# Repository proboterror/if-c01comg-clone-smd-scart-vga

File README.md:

IF-C01COMG Clone board SMD Full size - with SCART and DSUB-15 (VGA 15KHz) inputs.<br>
Separate H/V and combined sync supported for DSUB-15 input.

BNC connectors option removed<br>
RCA audio connectors replaced with 3.5 mm audio jack<br>
Switches changed to ALPS SPUJ190900 / SPUJ193700<br>

Project migrated to KiCad 8.

## Bill of materials
|Reference|Value|Footprint|Qty|Manufacturer|SKU|
|-----|-----|-----|-----|-----|-----|
|C101,C102,C103|47uF/25V|6.3x5.4|3|PANASONIC|EEEFK1H470XP|
|||||PANASONIC|EEEFK1E470P|
|||||PANASONIC|EEEFK1E470P|
|C104,C105|10uF/50V|5x5.4|2|PANASONIC|EEEFK1H100UR|
|C114,C116,C117,C118,C119,C206|100nF|805|6|MURATA|GRM21BR71H104KA01L|
|C115,C207|100uF/16V|6.3x5.4|2|PANASONIC|EEEFK1C101P|
|C120,C122|10uF/25V|5x5.4|2|PANASONIC|EEEFK1H100UR|
|C121|1uF/25V|805|1|SAMSUNG|CL21B105KBFNNNE|
|C201,C202,C205|180pF|805|3|MURATA|GRM2165C1H181J|
|C203|1uF/50V|4x5.4|1|JB Capacitors|JCK1H010M040054|
|C204|39pF|805|1|MURATA|GRM2165C1H390J|
|D101,D102,D103,D104,D105,D106,D107,D108,D109,D110|BAT46-TR (BAT46W)|SOD-123|10|Diodes|BAT46W-7-F|
|D201|BZT52C12 (12V Zener)|SOD-123|1|Diodes|BZT52C12|
|F1|1812L050PR|Fuse_1812_4532Metric|1|Littlefuse|1812L050PR|
|J1|Conn_02x25_Odd_Even|Pin_Header_Angled_2x25_Pitch2.54mm|1|Connfly|BH-50R (DS1013-50R) (IDC-50MR)|
|J2|SCART-F||1|NINIGI|SCART-17|
|J5|DE15||1||DB15 Female Pins offset 8.5 mm Rows step 2.54 mm|
|J6|SJ1-3535NG||1|KLS Electronic|KLS1-TSJ3.5-008CBA (ST-215N-03)|
|||||KLS Electronic|KLS1-TSJ3.5-008DC (ST-215N-04)|
|||||Dragon City|ST-215N-03/ST-215N-04/ST-215N-03-SL|
|K1|G6K-2PY-12DC||1|OMRON|G6K-2PY-12DC|
|Q101,Q105,Q109,Q113,Q114,Q201|BC850C|SOT-23|6|Diotec|BC850C|
|R1,R2|470R|805|2|YAGEO|RC0805FR-07470RL|
|R3|20K|805|1|ROYAL OHM|0805S8F2002T5E|
|R101,R115,R129,R143,R152|75|805|5|ROYAL OHM|0805S8F750JT5E|
|R104,R114,R118,R128,R132,R142,R146,R155|100|805|8|YAGEO|RC0805FR-07100RL|
|R105,R119,R133,R203|56k|805|4|YAGEO|RC0805FR-0756KL|
|R106,R120,R134,R147,R148,R156,R157|33k|805|7|YAGEO|RC0805FR-0733KL|
|R107,R121,R135|1.5k|805|3|ROYAL OHM|0805S8F1501T5E|
|R113,R127,R141|390|805|3|YAGEO|RC0805FR-07390RL|
|R149,R158,R205|2.7k|805|3|YAGEO|RC0805FR-072K7L|
|R202|1K|805|1|ROYAL OHM|0805S8F1001T5E|
|R204|68K|805|1|YAGEO|RC0805FR-0768KL|
|SW1|SW_DPDT_x2||1|ALPS|SPUJ190900|
|SW2|SPUJ193700||1|ALPS|SPUJ193700|
|U1|NCP1117-12_SOT223|SOT-223|1|ONSEMI|NCP1117ST12T3G|

IF-C01COMG Clone board SMD Full size

This is a full sized version of the IF-C01COMG board for JVC pro monitors (TM-Hxx50CG) and some others...

It's basically the THT base board I made some months ago, with most components changed to SMD.

Credit goes to James Vanderloeff for the dual input idea.

Board is for now completely untested...

Finally this is a Kicad 5.1 project :D

You're welcome to clone, sell, re-design and whatever, see LICENSE.

(2021) Martin Hejnfelt (martin@hejnfelt.com)
This work is free. You can redistribute it and/or modify it under the
terms of the Do What The Fuck You Want To Public License, Version 2,
as published by Sam Hocevar. See the LICENSE file for more details.

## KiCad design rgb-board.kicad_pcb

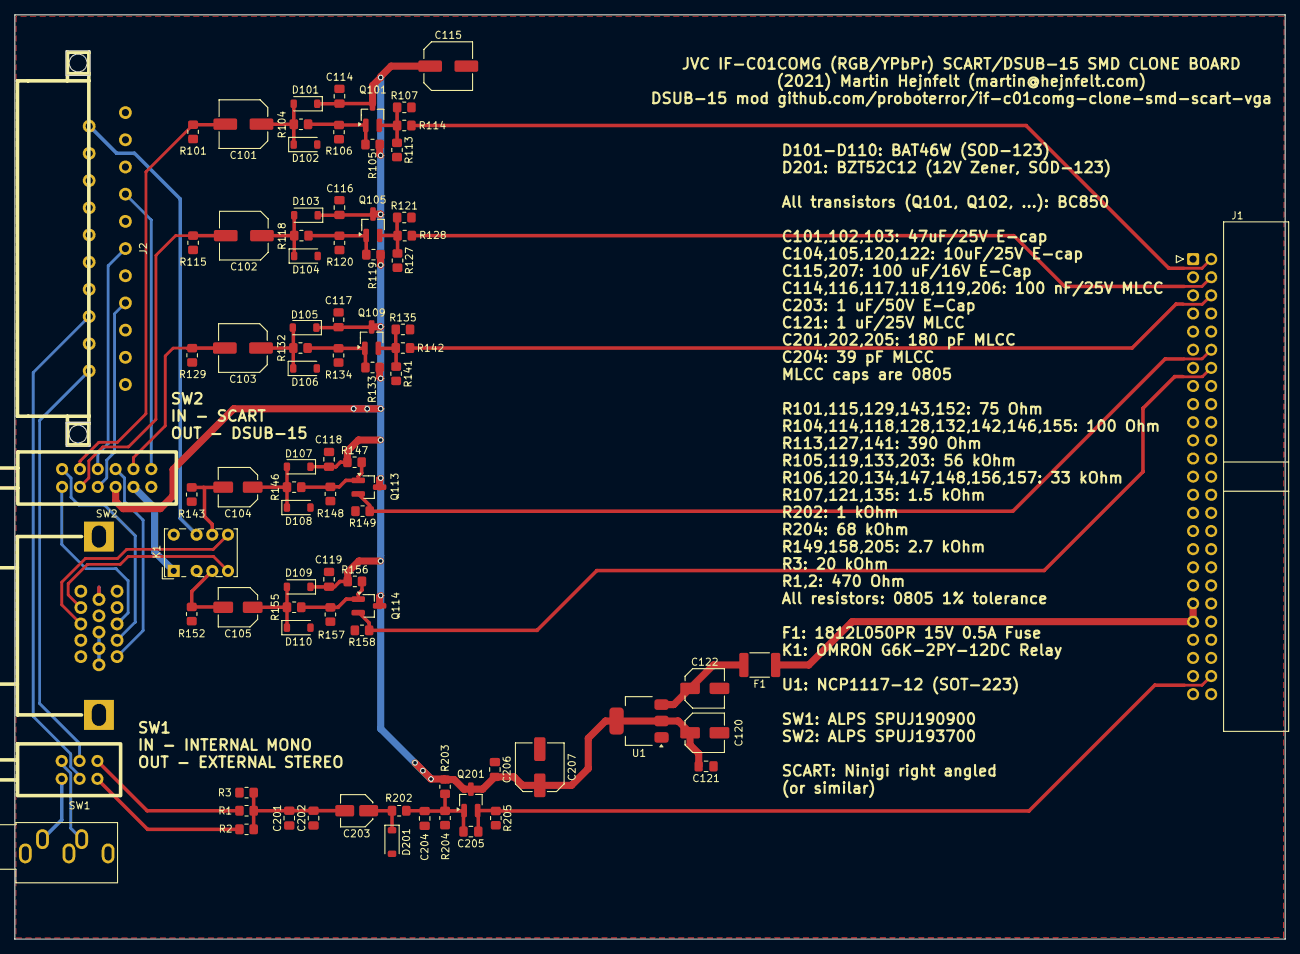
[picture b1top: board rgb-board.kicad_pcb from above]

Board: 2 copper layers, 178.0 x 129.5 mm, 85 parts (0 on the bottom side), 47 nets.

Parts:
C101, C102, C103: 47uF/25V; C_Elec_6.3x5.4
C104, C105: 10uF/50V; C_Elec_5x5.4
C114, C116, C117, C118, C119, C206: 100nF; C_0805_2012Metric_Pad1.18x1.45mm_HandSolder
C115, C207: 100uF/16V; C_Elec_6.3x5.4
C120, C122: 10uF/25V; C_Elec_5x5.4
C121: 1uF/25V; C_0805_2012Metric_Pad1.18x1.45mm_HandSolder
C201, C202, C205: 180pF; C_0805_2012Metric_Pad1.18x1.45mm_HandSolder
C203: 1uF/50V; C_Elec_4x5.4
C204: 39pF; C_0805_2012Metric_Pad1.18x1.45mm_HandSolder
D101, D102, D103, D104, D105, D106, D107, D108, D109, D110: BAT46-TR; D_SOD-123
D201: D_Zener; D_SOD-123
F1: 1812L050PR; Fuse_1812_4532Metric_Pad1.30x3.40mm_HandSolder
J1: Conn_02x25_Odd_Even; IDC-Header_2x25_P2.54mm_Horizontal
J2: SCART-F; NINIGI-SCART-RA
J5: DE15_Plug_HighDensity_MountingHoles; HD15-VGA
J6: SJ1-3535NG; Jack_3.5mm_CUI_SJ1-3535NG_Horizontal
K1: G6K-2PY-12DC; Relay_DPDT_Omron_G6K-2P
Q101, Q105, Q109, Q113, Q114, Q201: BC850C; SOT-23_Handsoldering
R1, R2: 470R; R_0805_2012Metric_Pad1.20x1.40mm_HandSolder
R3: 20K; R_0805_2012Metric_Pad1.20x1.40mm_HandSolder
R101, R115, R129, R143, R152: 75; R_0805_2012Metric_Pad1.20x1.40mm_HandSolder
R104, R114, R118, R128, R132, R142, R146, R155: 100; R_0805_2012Metric_Pad1.20x1.40mm_HandSolder
R105, R119, R133, R203: 56k; R_0805_2012Metric_Pad1.20x1.40mm_HandSolder
R106, R120, R134, R147, R148, R156, R157: 33k; R_0805_2012Metric_Pad1.20x1.40mm_HandSolder
R107, R121, R135: 1.5k; R_0805_2012Metric_Pad1.20x1.40mm_HandSolder
R113, R127, R141: 390; R_0805_2012Metric_Pad1.20x1.40mm_HandSolder
R149, R158, R205: 2.7k; R_0805_2012Metric_Pad1.20x1.40mm_HandSolder
R202: 1K; R_0805_2012Metric_Pad1.20x1.40mm_HandSolder
R204: 68K; R_0805_2012Metric_Pad1.20x1.40mm_HandSolder
SW1: SW_DPDT_x2; SPUJ190900
SW2: SPUJ193700
U1: NCP1117-12_SOT223; SOT-223-3_TabPin2

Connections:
+12V: C114.2, C115.1, C116.2, C117.2, C118.2, C119.2, C120.1, C121.2, C206.2, C207.1, D101.1 (K), D103.1 (K), D105.1 (K), D107.1 (K), D109.1 (K), Q101.3 (C), Q105.3 (C), Q109.3 (C), Q113.3 (C), Q114.3 (C), Q201.3 (C), R105.1, R119.1, R133.1, R147.1, R156.1, R203.1, SW2.3 (B1), U1.2 (VO)
/AUDIO: C201.2, C202.2, C203.2, R1.1, R2.2, R3.1
/AUDIO_: C205.1, J1.48, Q201.2 (E), R205.1
/AUDIO_EXT_L: J6.T, SW1.3 (C)
/AUDIO_EXT_R: J6.R, SW1.6 (C)
/AUDIO_INT_L: R2.1, SW1.1 (A)
/AUDIO_INT_R: R1.2, SW1.4 (A)
/AUDIO_L: J2.6, SW1.2 (B)
/AUDIO_R: J2.2, SW1.5 (B)
/B-Y: J1.4, R128.2
/B/B-Y: C102.2, R115.1, SW2.5 (COM2)
/G/Y: C101.2, R101.1, SW2.11 (COM4)
/HD: J1.12, Q113.2 (E), R149.1
/HD/CS: C104.2, K1.6, R143.1
/H_SYNC: J5.13, K1.5
/R-Y: J1.6, R142.2
/R/R-Y: C103.2, R129.1, SW2.8 (COM3)
/SCART_B: J2.7, SW2.4 (A2)
/SCART_G: J2.11, SW2.10 (A4)
/SCART_R: J2.15, SW2.7 (A3)
/SCART_SYNC: J2.20, K1.7
/VCC+14V: F1.1, J1.39, J1.41
/VD: C105.2, K1.3, R152.1
/VD_: J1.14, Q114.2 (E), R158.1
/VGA_B: J5.3, SW2.6 (B2)
/VGA_G: J5.2, SW2.12 (B4)
/VGA_R: J5.1, SW2.9 (B3)
/VGA_SELECT: K1.1, SW2.2 (COM1)
/V_SYNC: J5.14, K1.4
/Y: J1.2, R114.2
GND: C114.1, C115.2, C116.1, C117.1, C118.1, C119.1, C120.2, C121.1, C122.2, C201.1, C202.1, C204.1, C206.1, C207.2, D102.2 (A), D104.2 (A), D106.2 (A), D108.2 (A), D110.2 (A), D201.2 (A), J1.1, J1.3, J1.5, J1.7, J1.11, J1.13, J1.19, J1.21, J1.25, J1.31, J1.47, J1.49, J1.50, J2.4, J2.5, J2.9, J2.13, J2.17, J2.18, J2.21, J5.5, J5.6, J5.7, J5.8, J5.10, J6.S, K1.8, R3.2, R101.2, R106.2, R107.2, R113.2, R115.2, R120.2, R121.2, R127.2, R129.2, R134.2, R135.2, R141.2, R143.2, R148.2, R149.2, R152.2, R157.2, R158.2, R204.2, R205.2, U1.1 (GND)
unnamed: C101.1, D101.2 (A), D102.1 (K), R104.2
unnamed: C102.1, D103.2 (A), D104.1 (K), R118.2
unnamed: C103.1, D105.2 (A), D106.1 (K), R132.2
unnamed: C104.1, D107.2 (A), D108.1 (K), R146.2
unnamed: C105.1, D109.2 (A), D110.1 (K), R155.2
unnamed: C203.1, D201.1 (K), R202.2
unnamed: Q101.1 (B), R104.1, R105.2, R106.1
unnamed: Q101.2 (E), R107.1, R113.1, R114.1
unnamed: Q105.1 (B), R118.1, R119.2, R120.1
unnamed: Q105.2 (E), R121.1, R127.1, R128.1
unnamed: Q109.1 (B), R132.1, R133.2, R134.1
unnamed: Q109.2 (E), R135.1, R141.1, R142.1
unnamed: Q113.1 (B), R146.1, R147.2, R148.1
unnamed: Q114.1 (B), R155.1, R156.2, R157.1
unnamed: C204.2, C205.2, Q201.1 (B), R202.1, R203.2, R204.1
unnamed: C122.1, F1.2, U1.3 (VI)

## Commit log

2026-02-18 Update project to KiCad 8.
2026-02-18 Remove BNC connectors.
2026-02-18 Add ALPS SPUJ Series SPUJ193700 4PDT switch. Custom Push Button 4PDT symbol from https://github.com/skumlos/bkm-129x-scart-vga Custom E-Switch PBH4UEE 4PDT switch footprint from https://github.com/sk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
2026-02-18 Add DSUB-15 VGA Connector. Custom footprint from https://github.com/skumlos/bkm-129x-scart-vga Note pins rows spacing 2.54 mm.
2026-02-18 Add OMRON G6K-2PY-12DC Miniature Relay Dual Pole DPDT.
2026-02-18 Remove audio RCA connectors.
2026-02-18 Add CUI Devices / SAME SKY Devices SJ1-353XNG Series Audio Jack 3.5 mm Female.
2026-02-18 Edit PCB edge.
2026-02-18 SCART / VGA switching schematic.
2026-02-18 Add ALPS SPUJ Series push switches footprints library. Replace LC2259 and PBH4UEE push switches with ALPS SPUJ190900 and SPUJ193700. Remove LC2259 and PBH4UEE footprints.
2026-02-18 Route PCB.
    +14V power line polyfuse added.
2026-02-18 Edit SCART connector footprint silkscreen.
2026-02-18 Add GND fill exclude zone for 2x25 IDC connector. Edit SW1 silkscreen description.
2026-02-18 Update footprints from KiCad global library.
2026-02-18 Update PCB silkscreen description.
2026-02-19 Correct R203, R205 resistors marking for BoM.
2026-02-19 Oval mounting holes for DSUB-15/VGA connector.
2026-02-24 Square mounting pads for DSUB-15.
2026-04-10 Fixed Relay_DPDT_Omron_G6K-2P footprint pins spacing according to datasheet. Footprint copied from KiCad 8.0.0 global library to project.
    Fixed BOM duplicated values.
2026-04-12 Update project description.
